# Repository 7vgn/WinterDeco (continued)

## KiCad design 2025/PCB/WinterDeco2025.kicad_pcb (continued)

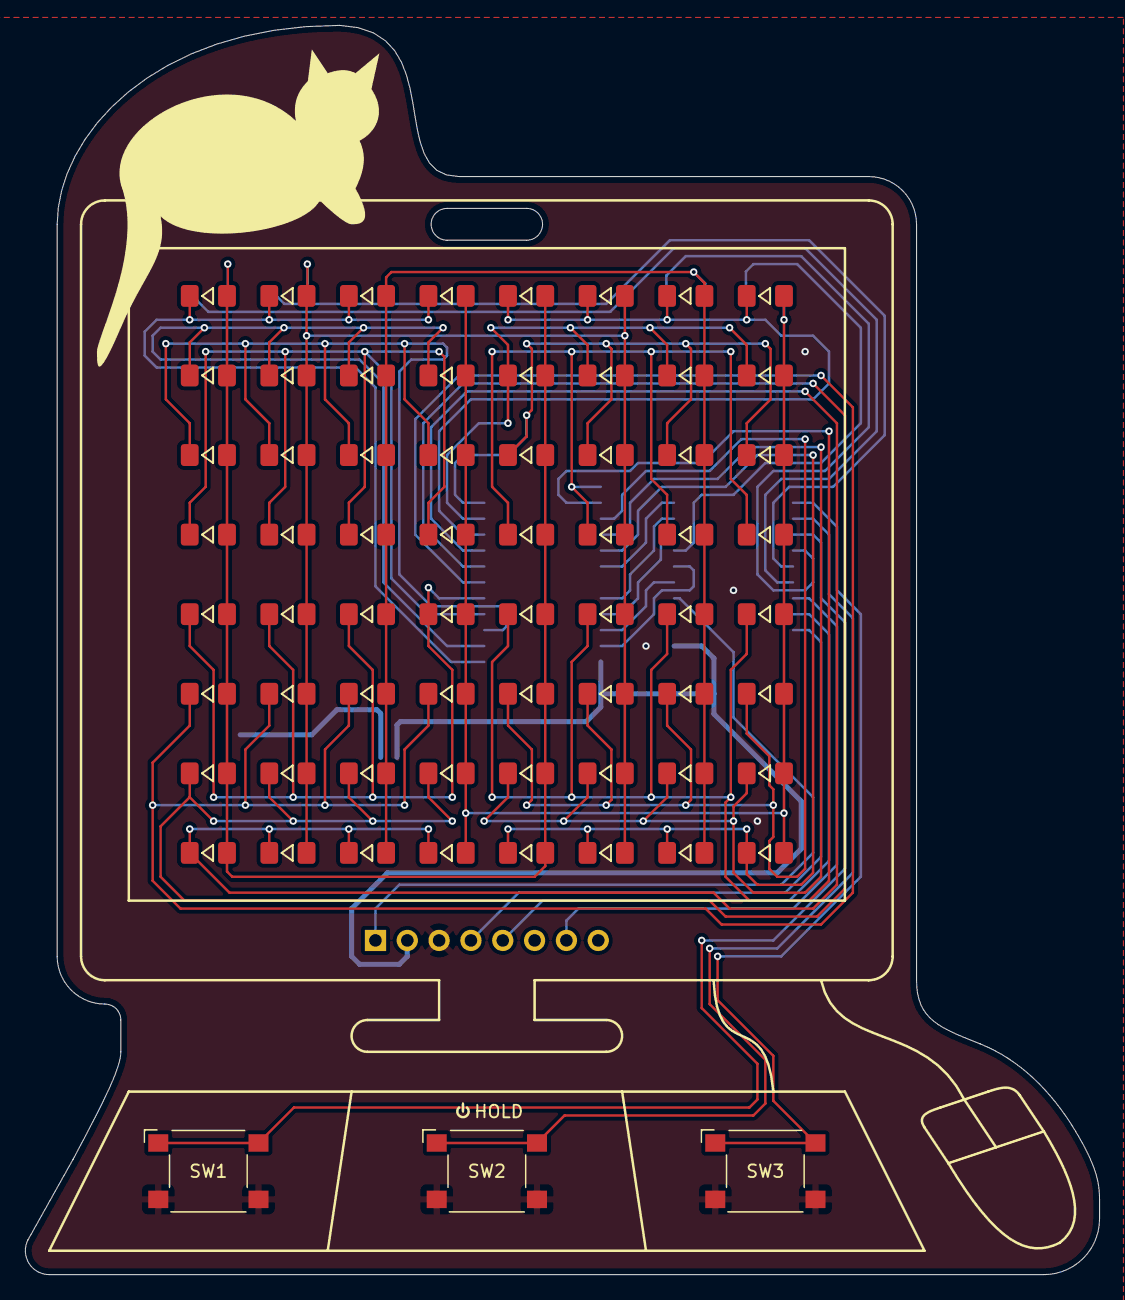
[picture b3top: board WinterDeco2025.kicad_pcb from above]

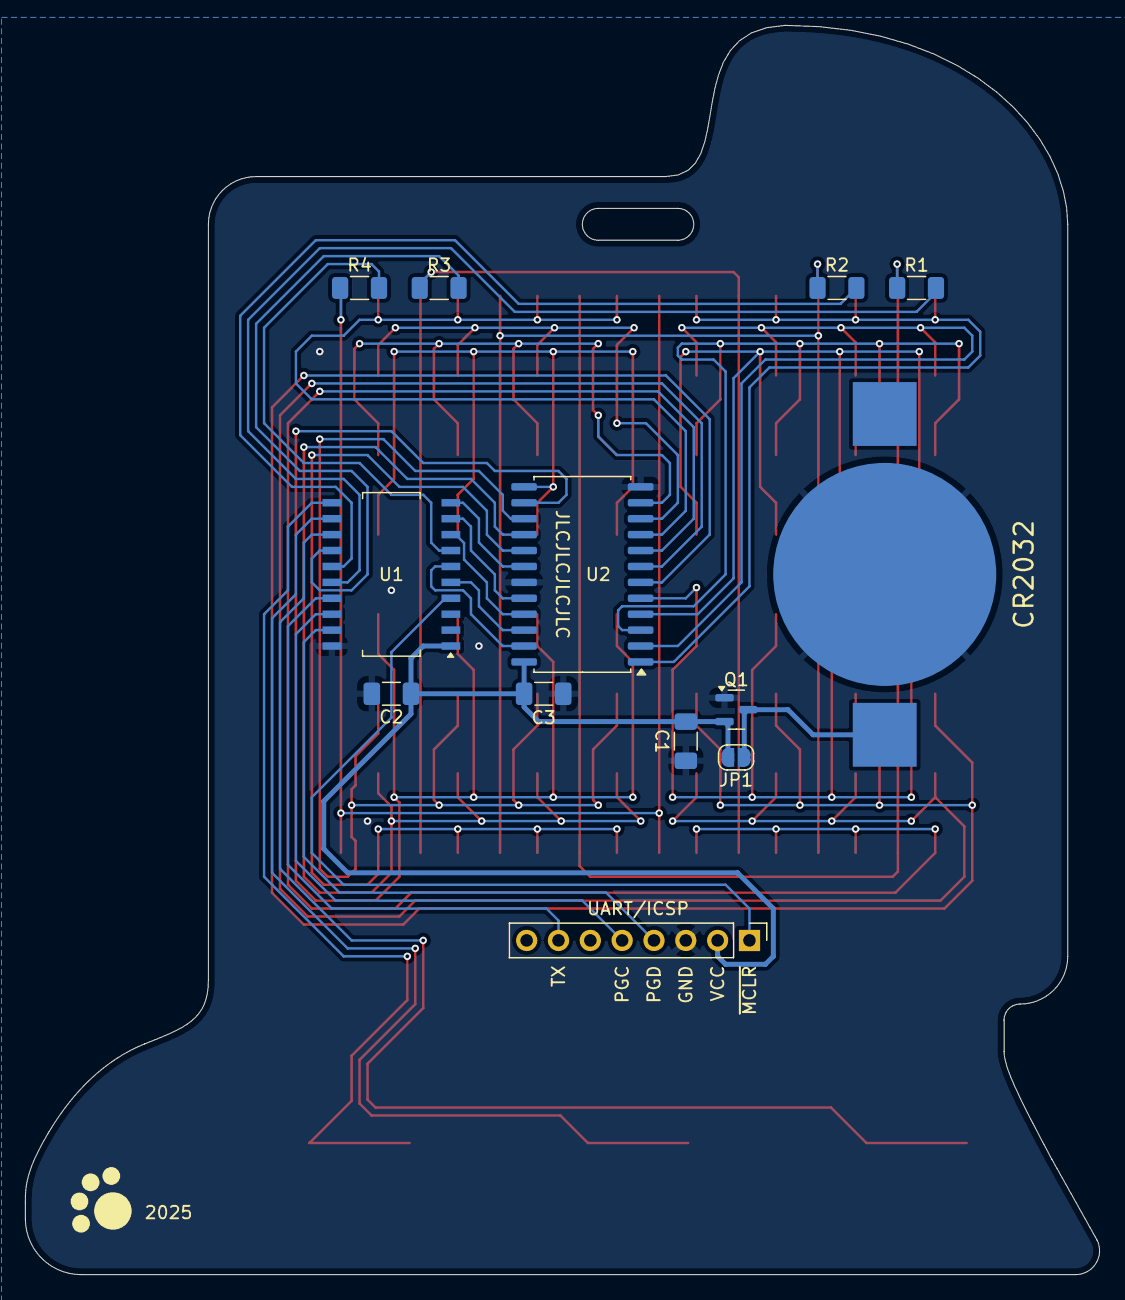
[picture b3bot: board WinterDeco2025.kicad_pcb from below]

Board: 2 copper layers, 85.7 x 99.7 mm, 80 parts (13 on the bottom side), 39 nets.

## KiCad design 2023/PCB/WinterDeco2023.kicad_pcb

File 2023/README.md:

# Winter Decoration 2023

The 2023 winter-themed decoration is an evergreen tree with lights. The PCB features a touch-sensitive button. A long press will turn the device on and off. When switched on, a short press cycles through the different programs. 

The touch sensor is implemented using the [PIC18F14Q41](https://www.microchip.com/en-us/product/pic18f14q41)'s capacitive voltage divider (CVD) feature. You can learn more about CVD in Microchip's Application Notes [1478](https://ww1.microchip.com/downloads/en/appnotes/01478A.pdf) and [2934](https://ww1.microchip.com/downloads/en/AppNotes/AN2934-Capacitive-Touch-Sensor-Design-Guidelines-00002934A.pdf). 

## Bill of Materials

| Ref | Qty | Part | Value | Links[^links]
| --- | ---:| --- | --- | --- |
| - | 1 | PCB | 2-layer, 1.6mm thickness, green soldermask, lead-free HASL | [J](https://jlcpcb.com/)
| BT1 | 1 | Battery Holder | CR2032, Keystone 103 | [M](https://mouser.com/ProductDetail/?qs=Q3RoVmURDolsdXuDGYj49g%3D%3D) [D](https://www.digikey.com/en/products/detail/keystone-electronics/103/331620) [R](https://www.reichelt.de/shop/produkt/knopfzellenhalter_fuer_20_mm-44621)
| C1 | 1 | Capacitor | SMD 1206, 100µF, X5R | [M](https://mouser.com/ProductDetail/?qs=pUKx8fyJudDzdyEEakAKPA%3D%3D) [D](https://www.digikey.com/en/products/detail/murata-electronics/GRM31CR60J107KEA8L/16286000?s=N4IgTCBcDaIOICUCyBmAjAYQQNgAwCk1cB2AaQFEBBADgBkQBdAXyA) [R](https://www.reichelt.de/shop/produkt/mlcc_1206_100_f_6_3_v_-10_x5r-409219)
| D* | 30 | LED | SMD 1206, yellow | [M](https://mouser.com/ProductDetail/?qs=sGAEpiMZZMv0DJfhVcWlK%252BdbpgZMtcHOeXAaxJ3bARo%3D) [D](https://www.digikey.com/en/products/detail/liteon/LTST-C150YKT/269217?s=N4IgTCBcDaIDIBUDKCC0BhAjAVgAwE0BpBEAXQF8g) [R](https://www.reichelt.de/shop/produkt/led_smd_1206_gelb_150_mcd_120_-361548)
| Q1[^polprot] | 1 | P-MOSFET | IRLML6402, SOT-23 | [M](https://mouser.com/ProductDetail/?qs=9%252BKlkBgLFf0HuZuONx2Ewg%3D%3D) [D](https://www.digikey.com/en/products/detail/infineon-technologies/IRLML6402TRPBF/811437) [R](https://www.reichelt.de/shop/produkt/mosfet_p-ch_-20v_-3_7a_0_065r_sot-23-108743)
| R1..3 | 3 | Resistor | SMD 1206, 68Ω | [M](https://mouser.com/ProductDetail/?qs=CteSnpDdeuDJTICysoGhNw%3D%3D) [D](https://www.digikey.com/en/products/detail/yageo/RC1206JR-0768RL/729330?s=N4IgTCBcDaIEoGECMYAMA2AUnAtKg7OgBxwAyIAugL5A) [R](https://www.reichelt.de/shop/produkt/smd-widerstand_1206_68_ohm_250_mw_5_-18364)
| R4 | 1 | Resistor | SMD 1206, 3.3kΩ | [M](https://mouser.com/ProductDetail/?qs=CteSnpDdeuDJAlQtfVL%252BIw%3D%3D) [D](https://www.digikey.com/en/products/detail/yageo/RC1206JR-073K3L/729267?s=N4IgTCBcDaIEoGECMYAMA2AUnAtKg7AMwDShAMiALoC%2BQA) [R](https://www.reichelt.de/shop/produkt/smd-widerstand_1206_3_3_kohm_250_mw_5_-18302)
| R5 | 1 | Resistor | SMD 1206, 4.7kΩ | [M](https://mouser.com/ProductDetail/?qs=CteSnpDdeuDgOu3Rsm1uRA%3D%3D) [D](https://www.digikey.com/en/products/detail/yageo/RC1206JR-074K7L/729295?s=N4IgTCBcDaIEoGECMYAMA2AUnAtKg7ACwDS%2BAMiALoC%2BQA) [R](https://www.reichelt.de/shop/produkt/smd-widerstand_1206_4_7_kohm_250_mw_5_-18330)
| U1 | 1 | Microcontroller | PIC18F14Q41-I/SO, SOIC-14 | [M](https://mouser.com/ProductDetail/?qs=W%2FMpXkg%252BdQ5jNCMT7LkJWg%3D%3D) [D](https://www.digikey.com/en/products/detail/microchip-technology/PIC18F14Q41-I-SO/13415037?s=N4IgTCBcDaIA4EsDGBGAHAMxQFgI7ZQFoEB6AZwHsQBdAXyA) [R](https://www.reichelt.de/shop/produkt/8-bit-picmicro_mikrocontroller_16_kb_64_mhz_so-20-311092)
| - | 1 | Piece of String | |
| - | 1 | Coin Cell | CR2032 |

[^links]: Links are just examples. Other sellers are available and similar parts can be substituted.  
[^polprot]: Q1 protects against reverse polarity and is optional. If left out, the solder jumper JP1 must be bridged instead. 

Required tools and materials: soldering iron, lead-free solder, tweezers, flux, isopropyl alcohol for cleaning, PIC programmer

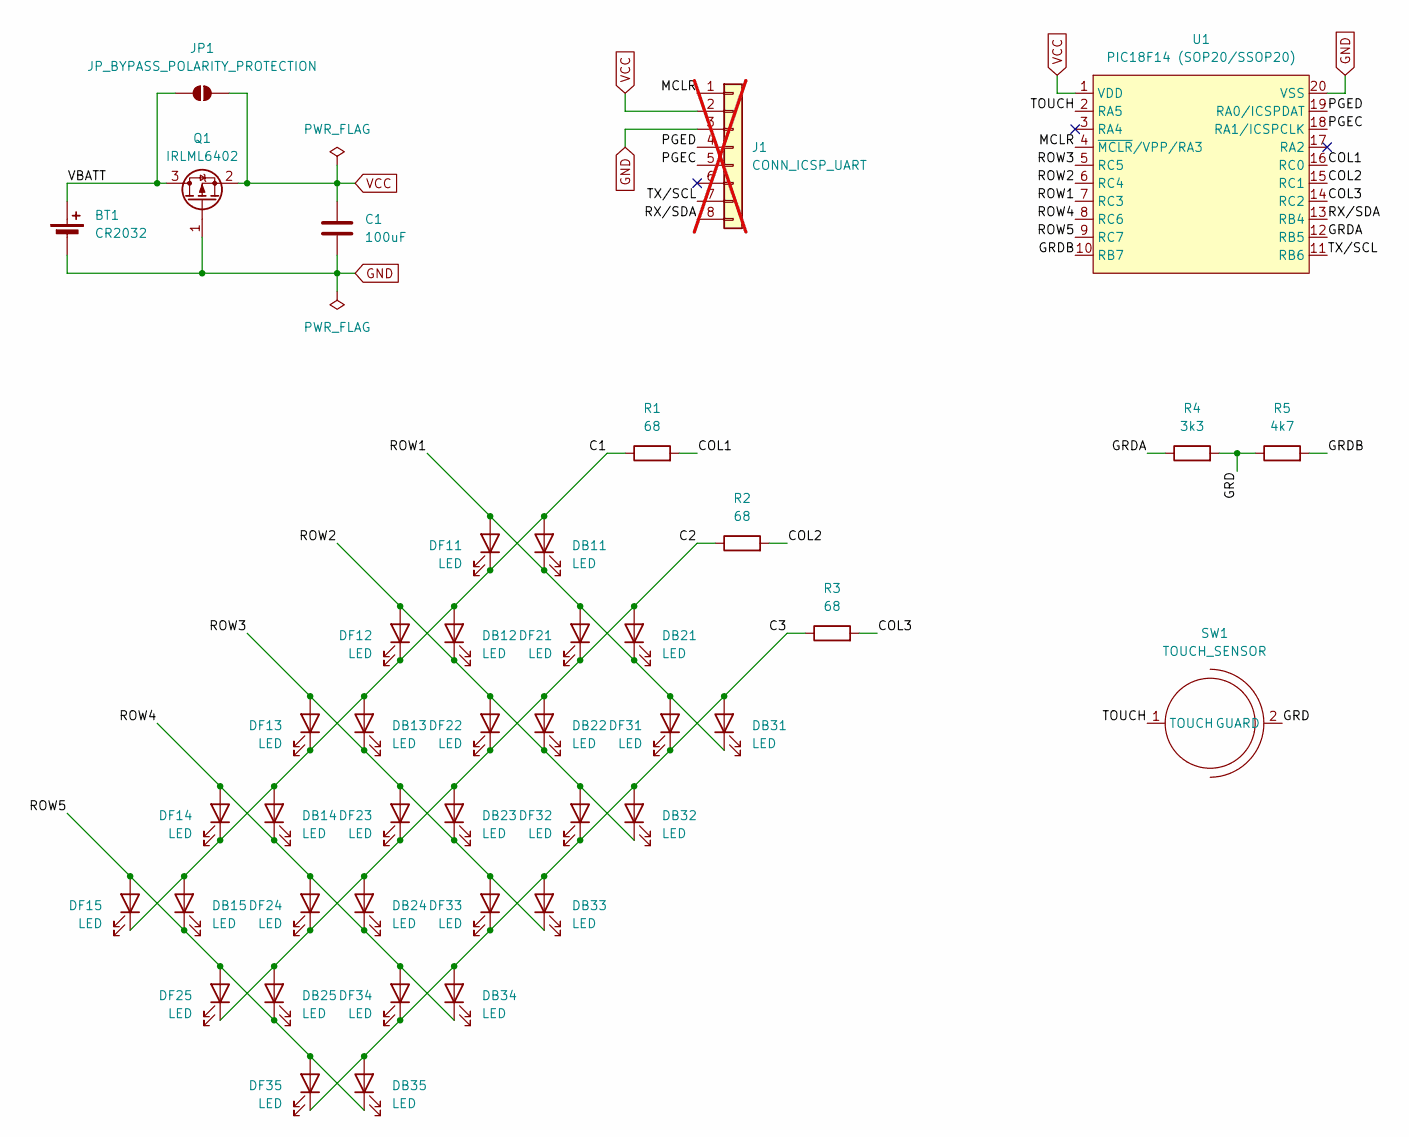
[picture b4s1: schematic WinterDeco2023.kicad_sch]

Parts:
BT1: CR2032; BatteryHolder_Keystone_103_1x20mm
C1: 100uF; C_1206_3216Metric_Pad1.33x1.80mm_HandSolder
DB11, DB12, DB13, DB14, DB15, DB21, DB22, DB23, DB24, DB25, DB31, DB32, DB33, DB34, DB35: LED; LED_1206_3216Metric_Pad1.42x1.75mm_Arrow_HandSolder
DF11, DF12, DF13, DF14, DF15, DF21, DF22, DF23, DF24, DF25, DF31, DF32, DF33, DF34, DF35: LED; LED_1206_3216Metric_Pad1.42x1.75mm_Arrow_HandSolder
J1: CONN_ICSP_UART; PinHeader_1x08_P2.54mm_Vertical; not fitted
JP1: JP_BYPASS_POLARITY_PROTECTION; SolderJumper-2_P1.3mm_Open_RoundedPad1.0x1.5mm
Q1: IRLML6402; SOT-23
R1, R2, R3: 68; R_1206_3216Metric_Pad1.30x1.75mm_HandSolder
R4: 3k3; R_1206_3216Metric_Pad1.30x1.75mm_HandSolder
R5: 4k7; R_1206_3216Metric_Pad1.30x1.75mm_HandSolder
SW1: TOUCH_SENSOR; Touch Sensor Thin
U1: PIC18F14 (SOP20/SSOP20); SO-20_12.8x7.5mm_P1.27mm

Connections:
/C1: DB11.2 (A), DB12.2 (A), DB13.2 (A), DB14.2 (A), DB15.2 (A), DF11.1 (K), DF12.1 (K), DF13.1 (K), DF14.1 (K), DF15.1 (K), R1.1
/C2: DB21.2 (A), DB22.2 (A), DB23.2 (A), DB24.2 (A), DB25.2 (A), DF21.1 (K), DF22.1 (K), DF23.1 (K), DF24.1 (K), DF25.1 (K), R2.1
/C3: DB31.2 (A), DB32.2 (A), DB33.2 (A), DB34.2 (A), DB35.2 (A), DF31.1 (K), DF32.1 (K), DF33.1 (K), DF34.1 (K), DF35.1 (K), R3.1
/COL1: R1.2, U1.16 (RC0)
/COL2: R2.2, U1.15 (RC1)
/COL3: R3.2, U1.14 (RC2)
/GRD: R4.2, R5.1, SW1.2 (GUARD)
/GRDA: R4.1, U1.12 (RB5)
/GRDB: R5.2, U1.10 (RB7)
/MCLR: J1.1, U1.4 (~MCLR/VPP/RA3)
/PGEC: J1.5, U1.18 (RA1/ICSPCLK)
/PGED: J1.4, U1.19 (RA0/ICSPDAT)
/ROW1: DB11.1 (K), DB21.1 (K), DB31.1 (K), DF11.2 (A), DF21.2 (A), DF31.2 (A), U1.7 (RC3)
/ROW2: DB12.1 (K), DB22.1 (K), DB32.1 (K), DF12.2 (A), DF22.2 (A), DF32.2 (A), U1.6 (RC4)
/ROW3: DB13.1 (K), DB23.1 (K), DB33.1 (K), DF13.2 (A), DF23.2 (A), DF33.2 (A), U1.5 (RC5)
/ROW4: DB14.1 (K), DB24.1 (K), DB34.1 (K), DF14.2 (A), DF24.2 (A), DF34.2 (A), U1.8 (RC6)
/ROW5: DB15.1 (K), DB25.1 (K), DB35.1 (K), DF15.2 (A), DF25.2 (A), DF35.2 (A), U1.9 (RC7)
/RX/SDA: J1.8, U1.13 (RB4)
/TOUCH: SW1.1 (TOUCH), U1.2 (RA5)
/TX/SCL: J1.7, U1.11 (RB6)
/VBATT: BT1.1 (+), JP1.1 (A), Q1.3 (D)
GND: BT1.2 (-), C1.2, J1.3, Q1.1 (G), U1.20 (VSS)
VCC: C1.1, J1.2, JP1.2 (B), Q1.2 (S), U1.1 (VDD)

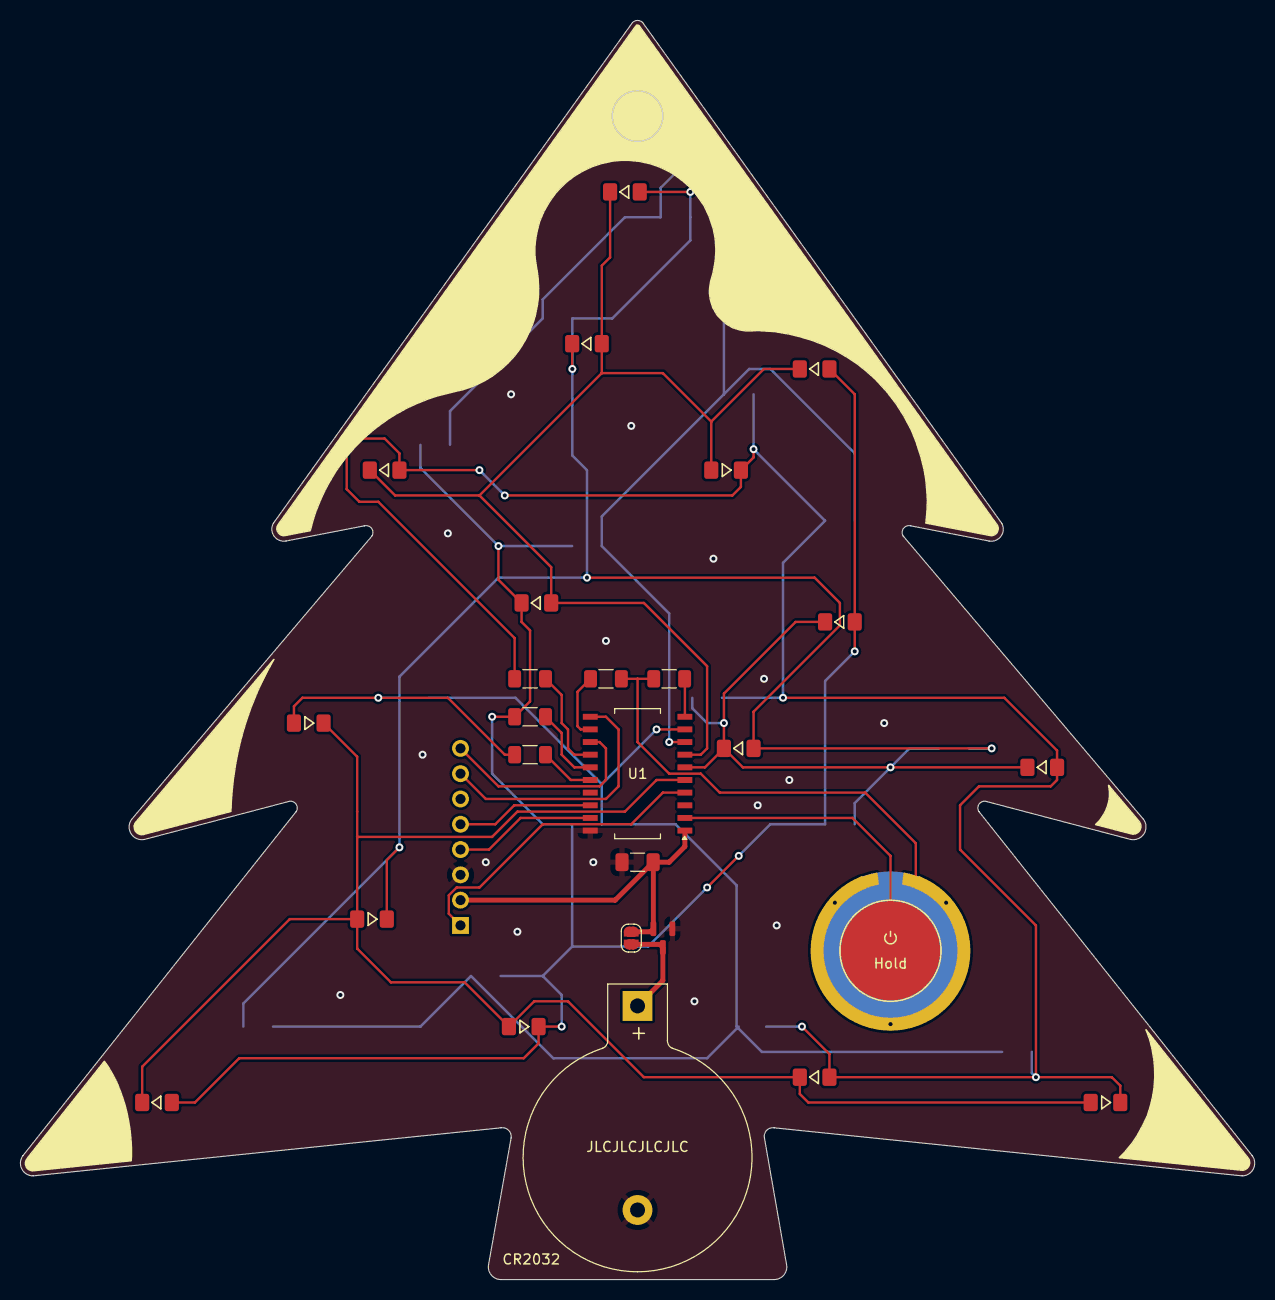
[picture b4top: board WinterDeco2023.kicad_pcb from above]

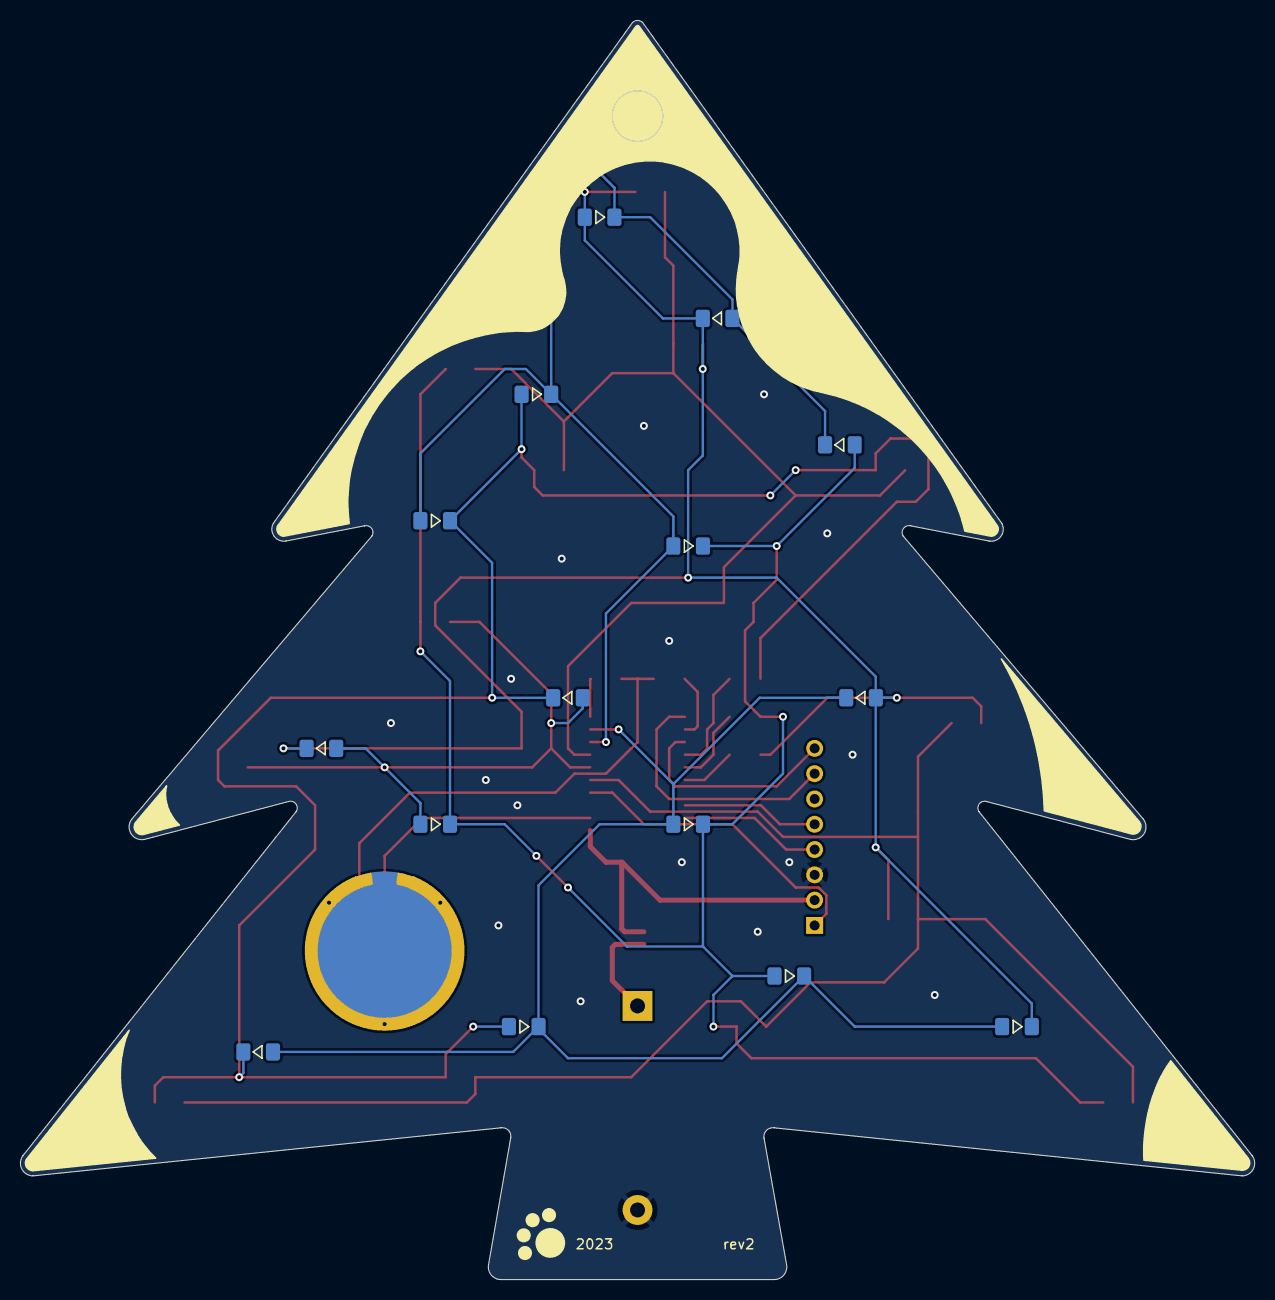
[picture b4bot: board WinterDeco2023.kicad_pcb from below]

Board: 2 copper layers, 124.0 x 126.4 mm, 42 parts (15 on the bottom side), 23 nets.

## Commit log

2025-09-26 Testing HTML file
2025-10-05 Testing markdown syntax
2025-10-05 Added 2023 PCB
2025-10-05 Fixed KiCAD ignores
2025-10-05 Fixed MPLAB X ignores
2025-10-06 Fixed swapped rows and columns
2025-10-06 Added PCBs
2025-10-06 Fixed table formatting
2025-10-06 Fixed microcontroller package and links
2025-10-25 Finished 2025 firmware
2025-10-25 Fixed overly broad ignore direcives
2025-10-25 Fixed typo
2025-10-27 Cosmetic corrections
2025-10-27 2023 Firmware
2025-10-27 Fixed compiler warnings
2025-10-27 Added 2024 Firmware
